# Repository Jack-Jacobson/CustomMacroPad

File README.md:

# Custom Macropad
## My first experience with designing PCBs and custom firmware by making a media control macropad. 

This is a 9-key macropad with an ESP32C3 dev module at it's core. It will be able to play, pause, control volume, skip, and have programmable macro keys. 

This project was intended to help me get into the hardware part of creation. I had to learn KiCad, CPP, and more to be able to make it. In the future I also plan on using these skills to make a full keyboard!

--- 

## Visuals
KiCad Circuit Schematic:

KiCad PCB layout:

3D Render:

Final Build:
Coming soon!

---

## Bill of Materials 

| Component | Quantity | Cost (w/ Shipping) | Description & Notes | Link |
| :--- | :---: | :---: | :--- | :--- |
| **ESP32-C3-DEVKITM-1-N4X** | 1 | $0.31 | Main computer (Amazon gift card applied to cover most) | [Amazon](https://www.amazon.com/gp/product/B0DHS5D9QR?smid=A33XZ36WFNH796&psc=1) |
| **Greetech Blue 55g clicky switch + Kailh Hot Swap Sockets** | 9 | $6.89 | For the macro board itself; hot-swap sockets used to avoid desoldering | [Mechanical Keyboards](https://mechanicalkeyboards.com/products/greetech-blue-55g-clicky?variant=47599969370412&country=US&currency=USD&utm_medium=product_sync&utm_source=google&utm_content=sag_organic&utm_campaign=sag_organic&com_cvv=8fb3d522dc163aeadb66e08cd7450cbbdddc64c6cf2e8891f6d48747c6d56d2c) |
| **PCB** | 5 *(min. order)* | $11.20 | Main custom PCB board base | [JLCPCB](https://jlcpcb.com/) |
| **Keycaps** | 10 *(min. order)* | $31.00 | Keycaps to make the project polished and tactile | [Yuzu Keycaps](https://yuzukeycaps.com/c/7f7ec5b1-1e28-4e48-ae13-4913c57327d8) |
| **Female Single Row Header Strips** | 5 *(min. offered)* | $7.52 | Used to cleanly socket and connect the dev board to the PCB | [eBay](https://www.ebay.com/itm/177501534620?chn=ps&norover=1&mkscid=101&itemid=177501534620&targetid=2450249296795&device=c&mktype=pla&googleloc=1014654&poi&campaignid=21214315381&mkgroupid=188184246123&rlsatarget=pla-2450249296795&abcId=9407526&merchantid=5411207311) |
| --- | --- | --- | --- | --- |
| **TOTALS** | **30 Items** | **$56.92** | *Project baseline hardware cost* | |

## Firmware and Setup

### Dependencies
* ESP32BLECombo by kokodev

### Build Instructions
1. Clone this repository (https://github.com/Jack-Jacobson/CustomMacroPad.git)
2. Open the repo in Arduino IDE or other IDE
3. Select your board (I chose ESP32C3)
4. Compile and flash device
5. You're good to go!

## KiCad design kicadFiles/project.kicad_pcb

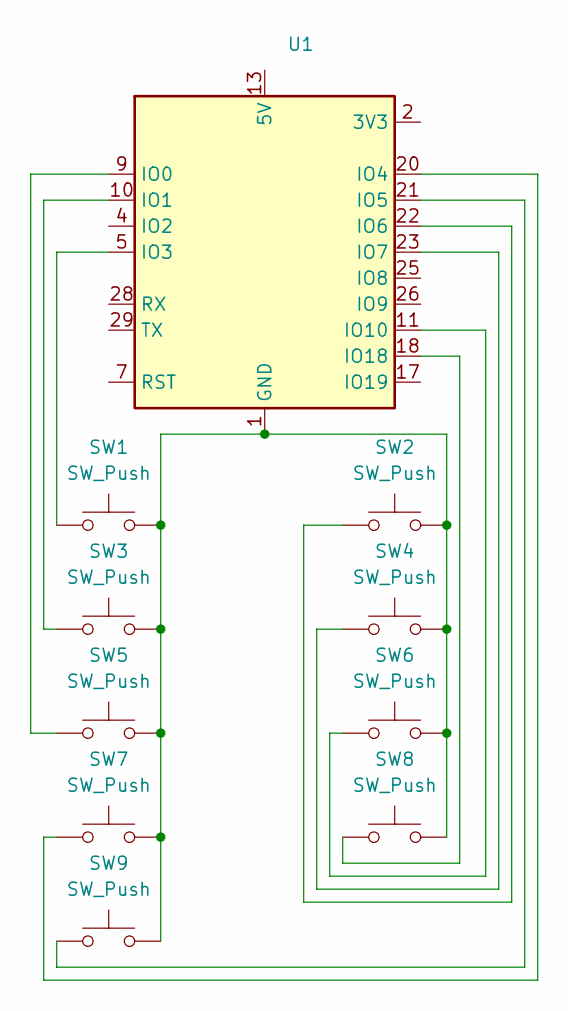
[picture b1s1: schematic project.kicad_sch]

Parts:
SW1, SW2, SW3, SW4, SW5, SW6, SW7, SW8, SW9: SW_Push; SW_Cherry_MX_1.00u_PCB
U1: ESP32-C3-DevKitM-1; PinHeader_1x15_P2.54mm_Vertical

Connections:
unnamed: SW1.2, SW2.2, SW3.2, SW4.2, SW5.2, SW6.2, SW7.2, SW8.2, SW9.2, U1.1 (GND), U1.6 (GND), U1.8 (GND), U1.12 (GND), U1.15 (GND), U1.16 (GND), U1.19 (GND), U1.24 (GND), U1.27 (GND), U1.30 (GND)
unnamed: U1.2 (3V3), U1.3 (3V3)
unnamed: U1.13 (5V), U1.14 (5V)
unnamed: SW5.1, U1.9 (IO0)
unnamed: SW3.1, U1.10 (IO1)
unnamed: SW1.1, U1.5 (IO3)
unnamed: SW7.1, U1.20 (IO4)
unnamed: SW9.1, U1.21 (IO5)
unnamed: SW2.1, U1.22 (IO6)
unnamed: SW4.1, U1.23 (IO7)
unnamed: SW6.1, U1.11 (IO10)
unnamed: SW8.1, U1.18 (IO18)

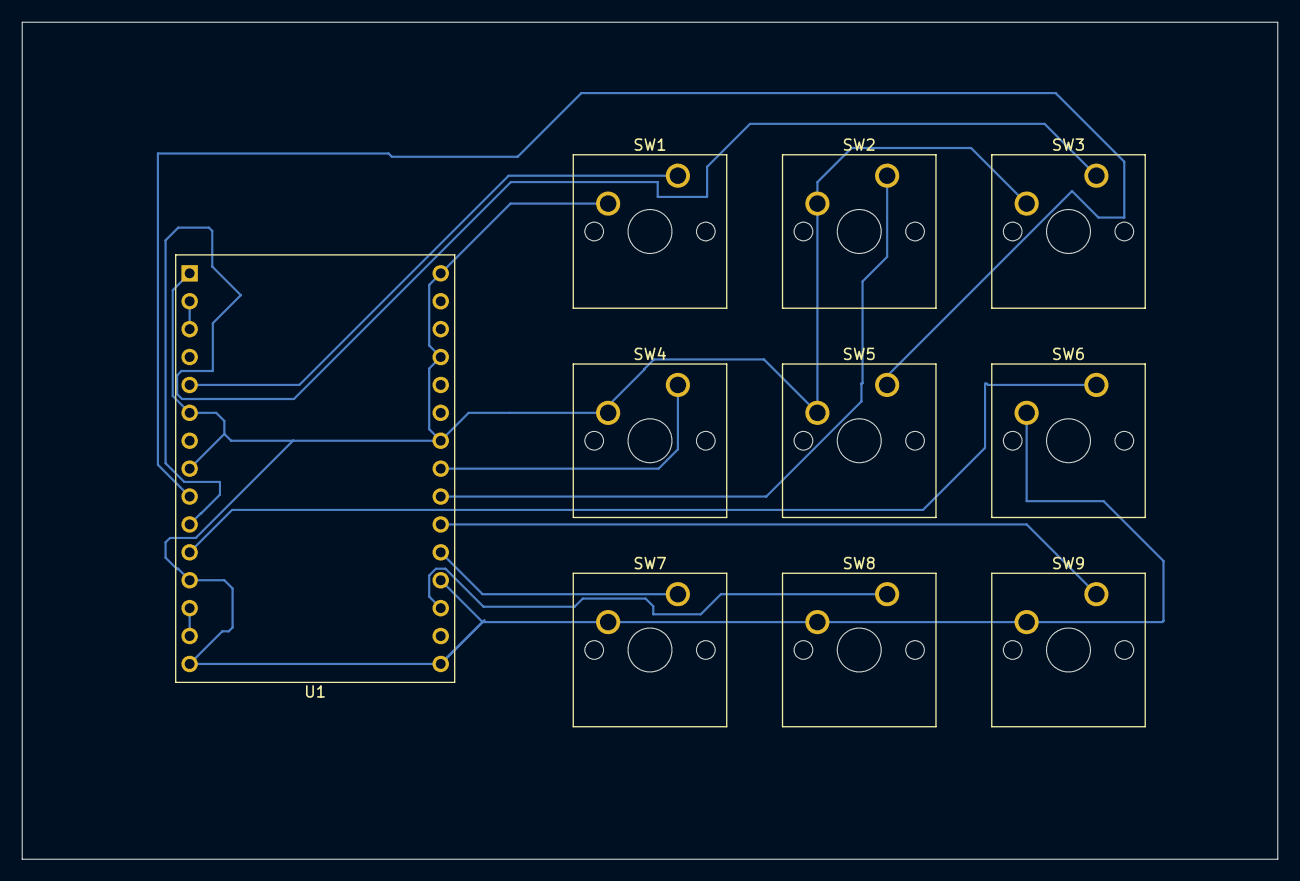
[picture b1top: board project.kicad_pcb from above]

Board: 2 copper layers, 114.3 x 76.2 mm, 10 parts (0 on the bottom side), 12 nets.
